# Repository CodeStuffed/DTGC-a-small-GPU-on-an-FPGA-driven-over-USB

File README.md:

# DTGC: a small GPU on an FPGA, driven over USB

DTGC is a graphics chip I am building on the Sipeed Tang Nano 20K FPGA board. A PC sends drawing commands over USB, the FPGA draws into memory, and the picture goes out over HDMI to a monitor.

**Status: nothing has run on real hardware yet.** Every result here comes from simulation (running the Verilog on a PC) or from the emulator (a Python copy of the GPU). "Passes simulation" never means "works on the board". Real results go in [docs/test-log.md](docs/test-log.md).

## The plan

1. **Basics.** Install free open-source FPGA tools, read the board's schematic, blink an LED, show colour bars over HDMI, and keep a picture in the board's SDRAM memory.
2. **Talk to a PC.** A USB protocol with checksums and retries, a parser on the FPGA, and a Python emulator of the GPU so software can be tested without a board.
3. **Draw in 3D.** A triangle rasterizer with depth test, colour blending and textures, then a spinning cube demo.
4. **Make it fast.** Measure a frame in simulation and remove the slowest parts one at a time.
5. **HD output.** 720p and 1080p, with an upscaler so 1080p fits the board's memory and speed. Target: 1080p at 30 fps.
6. **Make it useful.** An app window, small games, a graphics API, and a small Direct3D 9 bridge for old programs.
7. **Faster USB.** Windows and Linux app packages, and a link through an FT2232H USB 2.0 chip, much faster than the board's own serial port.
8. **A board for the fast link.** A small 4-layer "backpack" PCB with the FT2232H that plugs on top of the Tang Nano 20K.
9. **Ready to order.** A 3D-printed case, the files an assembly service needs, and a line-by-line check of the schematic against the chip's datasheet.
10. **Wrap up.** How to run and test everything, then real hardware tests.

Rules for the whole project: free tools only, every Verilog module gets a testbench, and no pin or voltage is guessed. Anything not yet confirmed is marked VERIFY.

## Progress log

Each update below was added when that step was finished. Older updates stay as they were written.

<!-- part 1 -->
### Update 1: Tools, first blink, colour bars and memory

The starting point: free tools, a check that they support this board, and the first three pieces of hardware design.

- **Tools.** Only free open-source tools: Yosys, nextpnr-himbaechel with Apicula, openFPGALoader and Icarus Verilog, all from the OSS CAD Suite. No vendor tools. Install steps are in [docs/setup.md](docs/setup.md), installed versions in [tools/versions.md](tools/versions.md), and what to buy in [docs/shopping-list.md](docs/shopping-list.md).
- **Board research.** Pins come from Sipeed's schematic, not from guesses. Any pin, voltage or timing not yet confirmed is marked VERIFY in [docs/verify.md](docs/verify.md). The pins used are in [docs/board/pins-needed.md](docs/board/pins-needed.md).
- **Blink an LED** (`rtl/blink.v`). The smallest test that the build and flash chain works. Passes simulation and the bitstream builds.
- **640x480 HDMI colour bars** (`rtl/video_timing.v`, `rtl/tmds_encoder.v`, `rtl/hdmi_out.v`). Screen timing plus TMDS, the encoding HDMI uses for each colour wire. Passes simulation and the bitstream builds.
- **SDRAM framebuffer** (`rtl/sdram_ctrl.v`, `rtl/fb_scanout.v`). The picture is kept in the board's SDRAM memory and read out to the screen. A memory model fails the test on any broken timing rule. Writing it found two mistakes: too few memory refreshes in the first plan, and stray pixels after reset.

The overall plan is in [docs/design-plan.md](docs/design-plan.md) and the milestone list in [docs/roadmap.md](docs/roadmap.md).

Next: get commands from a PC into the GPU, and a way to test without a board.

<!-- part 2 -->
### Update 2: USB protocol, emulator and tests

The GPU learns to take commands from a PC, and everything gets a test.

- **Protocol** ([docs/protocol.md](docs/protocol.md)). Binary packets with checksums, sequence numbers and retries. On the FPGA, `rtl/uart_rx.v` receives, `rtl/pkt_parser.v` checks each packet and `rtl/cmd_exec.v` runs it. The first UART version cut the stop bit short; the tests caught it.
- **Emulator** (`sw/dtgc/emulator.py`). A Python copy of the GPU that speaks the same protocol over TCP. It matches the Verilog bit for bit on random command streams, so software can be written and tested with no board.
- **Library and command line** (`sw/dtgc/`). Finds the board, or falls back on the emulator. Has a self-test, and record and replay.
- **Tests.** `python scripts/run_tests.py --quick` runs everything. [scripts/mutation_check.py](scripts/mutation_check.py) plants one bug at a time in the Verilog and checks that some test fails.
- **Saving link bandwidth.** Only changed tiles are sent, with run-length compression. A benchmark mode measures it: from 9 bytes per frame for a still picture up to 120,522 bytes for noise ([docs/benchmarks.md](docs/benchmarks.md)).

Next: draw triangles.

<!-- part 3 -->
### Update 3: Drawing triangles in 3D

- **Triangle rasterizer** (`rtl/raster.v`, [docs/rasterizer.md](docs/rasterizer.md)). Fixed-point maths for the triangle edges, colour blended across each triangle, a depth test so nearer things hide farther ones, and textures. Bit for bit the same as the Python reference.
- **Dither** ([docs/windows-and-color-options.md](docs/windows-and-color-options.md)). Smoother colour from few bits: 42.1 dB against 21.8 dB without dither.
- **Spinning cube demo.** `python -m sw.dtgc spin`. The picture above is what the Verilog drew in simulation, and it matches the emulator.

Size and speed of every build is recorded in [docs/resources.md](docs/resources.md).

Next: make drawing faster.

<!-- part 4 -->
### Update 4: Making it faster

Five speed steps, each measured in simulation on the same cube frame (340x340 picture):

| Step | Cube frame |
|---|---|
| Starting point (25.2 MHz clock) | about 46 ms |
| Keep SDRAM rows open | about 16 ms |
| One pixel per clock, burst depth reads | about 8 ms |
| Faster clears | about 5 ms |
| Fast depth clear, posted writes, skip empty space | 205,978 clocks down to about 88,000 |

Last, the drawing clock went from about 26 MHz to 46.41 and 48 MHz. That passes the timing estimate and simulation. The SDRAM pin timing is not checked yet (VERIFY).

Next: higher resolutions, up to 1080p.

<!-- part 5 -->
### Update 5: HD output and 1080p30

- **More resolutions.** 1280x720 at 60 Hz and 1920x1080 at 50 Hz. The fast serial clocks these need are untested against the chip's limits (VERIFY).
- **Upscalers** ([docs/upscale.md](docs/upscale.md)). A Python model first (DT-Upscale), then a bilinear upscaler and an edge-directed x2 upscaler in Verilog. Both match the model bit for bit. No neural networks.
- **Indexed triangle lists.** A corner shared by several triangles is sent once. The 1148-triangle field scene needs 3.43 times fewer bytes.
- **1080p at 30 fps** ([docs/architecture-1080p30.md](docs/architecture-1080p30.md)). The GPU draws a 960x540 picture and the edge upscaler doubles it to 1920x1080 on the way out. Drawing every pixel at full size does not fit the board's memory or time ([docs/hd-limits.md](docs/hd-limits.md)).

```mermaid
flowchart LR
  PC["PC app"] -- "USB" --> RX["Link and packet parser"]
  RX --> EXEC["Command executor"]
  EXEC --> RAST["Triangle rasterizer"]
  EXEC --> SDRAM[("SDRAM<br/>colour + depth")]
  RAST --> SDRAM
  SDRAM --> SCAN["Scan-out"]
  SCAN --> UP["Upscaler x2"]
  UP --> TMDS["HDMI encoder"]
  TMDS --> MON["Monitor"]
  EXEC -- replies --> PC
```

Two clock domains: drawing at 46.41 MHz, video at 74.25 MHz with a 371.25 MHz serial clock.

| Measured in simulation | Result |
|---|---|
| Spinning cube, 1080p30 build | 255,780 clocks, 5.51 ms |
| Field of 1148 triangles, 1080p30 build | 1,521,436 clocks, 32.8 ms, 30.5 fps (1.6% inside the budget) |
| Largest build, `top_gpu_1080p30` | 12,740 of 20,736 LUTs (61%), 10 of 46 block RAMs, core clock estimate 54.52 MHz (needs 46.41) |

What to check first on a real board: [docs/first-hardware.md](docs/first-hardware.md).

Next: an app and a graphics API so programs can use the GPU.

<!-- part 6 -->
### Update 6: Apps, games and the graphics API

- **Shader** (`rtl/shade_pipe.v`). A pipelined fixed-point shader that matches its model bit for bit. Built and tested, not yet connected to the GPU.
- **App and games.** `python -m sw.dtgc app` opens one window for everything. `python -m sw.dtgc play pong` runs a game. Tested on the emulator only.
- **Graphics API** ([docs/api.md](docs/api.md)). Canvas, meshes and frames for your own programs.
- **Three versions** ([docs/versions.md](docs/versions.md)). One app runs all three:

| | This PC only | Board, HDMI out | Board, USB out |
|---|---|---|---|
| What you need | Nothing extra | Tang Nano 20K, HDMI cable, monitor | Tang Nano 20K |
| Who draws | The PC's own graphics card | The FPGA | The FPGA |
| Where the picture goes | A window | A monitor | A window on the PC |

- **Direct3D 9 subset** ([docs/direct3d.md](docs/direct3d.md)). A small `d3d9.dll` so some old fixed-function Direct3D 9 programs can draw on DTGC. Modern games will not run.

Next: app packages and a faster USB link.

<!-- part 7 -->
### Update 7: Windows packages and the fast USB link

- **Windows device** ([docs/windows-device.md](docs/windows-device.md)). A software device so DTGC shows in Device Manager. Untested, because it needs admin rights.
- **App packages** ([docs/driver-app.md](docs/driver-app.md)). `scripts/package_windows.py` builds a portable `dtgc.exe` (its self-test passes). `scripts/package_linux.py` builds a Linux package, which has not been run on Linux.
- **FT2232H link** (`rtl/ft_link.v`, `rtl/top_gpu_ft.v`). The board's own USB serial port is assumed at about 0.3 MB/s (not yet measured), which gives about 19.5 fps for the field scene. The FT2232H chip moves 8 bits at a time at 60 MHz, up to about 40 MB/s by its datasheet. The whole GPU with this link passes simulation. It must pass the breakout test in [docs/ft2232h-test.md](docs/ft2232h-test.md) before any board is ordered.

Next: a small board that carries the fast USB chip.

<!-- part 8 -->
### Update 8: The xDTGC backpack board

A small 4-layer board that plugs on top of the Tang Nano 20K and carries the FT2232H. One USB-C cable powers both boards and carries the data. It does not add drawing power or change the HDMI resolution; it only makes the link faster.

| Item | Value |
|---|---|
| Size | 54.04 x 25 mm, the same length as the Tang Nano 20K |
| Layers | 4: top signals, ground, 3.3 V, bottom signals |
| Main chips | FT2232HL (USB to FIFO), 93LC56B (settings memory), AP2114H-3.3 (3.3 V regulator) |
| Protection | 500 mA resettable fuse, USB ESD diode, Schottky diode so two USB cables cannot fight |
| Fitting | Two 1x20 sockets underneath plug onto the Tang's pins |
| Files | `pcb/backpack/tinygpu_backpack.kicad_sch` (schematic) and `pcb/backpack/tinygpu_backpack.kicad_pcb` (layout), KiCad 10 |

The layout is made by scripts, so it can be rebuilt the same way every time: `scripts/pcb_place.py` places the parts and `scripts/pcb_route.py` routes them. The schematic rule check gives 0 errors and the layout rule check 0 errors, 0 unconnected. The layout review list is [docs/pcb-layout-review.md](docs/pcb-layout-review.md), and how assembly services work is in [docs/pcb-assembly.md](docs/pcb-assembly.md).

Next: a case, the order files, and a careful check of the schematic.

<!-- part 9 -->
### Update 9: Case, order files and datasheet review

- **Case** (`pcb/case/`, [docs/case.md](docs/case.md)). A 3D-printable tray and lid. Its sizes are placeholders until the real boards are measured, so do not print it yet.
- **Order files** (`pcb/backpack/quote/`). Gerbers, BOM and part positions, made by `python scripts/pcb_quote_pack.py`, which stops if the rule check finds any error. 39 parts on 20 BOM lines, about USD 12.86 per board at cached prices. Not a quote, and stock is not checked. Quote notes: [docs/pcbway-quote.md](docs/pcbway-quote.md).
- **Datasheet review.** The schematic was checked line by line against the FT2232H datasheet (version 2.3). That fixed four mistakes the automatic checks passed: two filter capacitors on the wrong side of their beads, the settings-memory pull-up on the wrong side of its resistor, the reset pin tied straight to 3.3 V, and a regulator that needed capacitors this board does not use. The board was then re-routed with no vias inside pads: 122 vias, 0.20 mm drill. The USB pair is 0.25 mm tracks with a 0.25 mm gap, about 93 ohm by hand formula (target 90). Lessons from all this: [docs/lessons.md](docs/lessons.md).

Before ordering:

1. Test the FT2232H on a breakout module with jumper wires ([docs/ft2232h-test.md](docs/ft2232h-test.md)). Expected: data passes both ways with no errors. If it fails, do not order.
2. Measure the real Tang Nano 20K. Expected: 20.32 mm between the two pin rows, and the tallest part lower than the 8.5 mm sockets.
3. Review the layout with [docs/pcb-layout-review.md](docs/pcb-layout-review.md).
4. Get a quote. Expected: the fab accepts the 0.20 mm vias and gives a USB pair impedance near 90 ohm.
5. Check stock of all 20 BOM lines on order day.

After the boards arrive, test them with [docs/pcb-home-test.md](docs/pcb-home-test.md).

Next: write up how to run everything.

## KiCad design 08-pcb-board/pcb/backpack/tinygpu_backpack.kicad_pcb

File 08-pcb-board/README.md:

# DTGC: a small GPU on an FPGA, driven over USB

DTGC is a graphics chip I am building on the Sipeed Tang Nano 20K FPGA board. A PC sends drawing commands over USB, the FPGA draws into memory, and the picture goes out over HDMI to a monitor.

**Status: nothing has run on real hardware yet.** Every result here comes from simulation (running the Verilog on a PC) or from the emulator (a Python copy of the GPU). "Passes simulation" never means "works on the board". Real results go in [docs/test-log.md](docs/test-log.md).

## The plan

1. **Basics.** Install free open-source FPGA tools, read the board's schematic, blink an LED, show colour bars over HDMI, and keep a picture in the board's SDRAM memory.
2. **Talk to a PC.** A USB protocol with checksums and retries, a parser on the FPGA, and a Python emulator of the GPU so software can be tested without a board.
3. **Draw in 3D.** A triangle rasterizer with depth test, colour blending and textures, then a spinning cube demo.
4. **Make it fast.** Measure a frame in simulation and remove the slowest parts one at a time.
5. **HD output.** 720p and 1080p, with an upscaler so 1080p fits the board's memory and speed. Target: 1080p at 30 fps.
6. **Make it useful.** An app window, small games, a graphics API, and a small Direct3D 9 bridge for old programs.
7. **Faster USB.** Windows and Linux app packages, and a link through an FT2232H USB 2.0 chip, much faster than the board's own serial port.
8. **A board for the fast link.** A small 4-layer "backpack" PCB with the FT2232H that plugs on top of the Tang Nano 20K.
9. **Ready to order.** A 3D-printed case, the files an assembly service needs, and a line-by-line check of the schematic against the chip's datasheet.
10. **Wrap up.** How to run and test everything, then real hardware tests.

Rules for the whole project: free tools only, every Verilog module gets a testbench, and no pin or voltage is guessed. Anything not yet confirmed is marked VERIFY.

## Progress log

Each update below was added when that step was finished. Older updates stay as they were written.

<!-- part 1 -->
### Update 1: Tools, first blink, colour bars and memory

The starting point: free tools, a check that they support this board, and the first three pieces of hardware design.

- **Tools.** Only free open-source tools: Yosys, nextpnr-himbaechel with Apicula, openFPGALoader and Icarus Verilog, all from the OSS CAD Suite. No vendor tools. Install steps are in [docs/setup.md](docs/setup.md), installed versions in [tools/versions.md](tools/versions.md), and what to buy in [docs/shopping-list.md](docs/shopping-list.md).
- **Board research.** Pins come from Sipeed's schematic, not from guesses. Any pin, voltage or timing not yet confirmed is marked VERIFY in [docs/verify.md](docs/verify.md). The pins used are in [docs/board/pins-needed.md](docs/board/pins-needed.md).
- **Blink an LED** (`rtl/blink.v`). The smallest test that the build and flash chain works. Passes simulation and the bitstream builds.
- **640x480 HDMI colour bars** (`rtl/video_timing.v`, `rtl/tmds_encoder.v`, `rtl/hdmi_out.v`). Screen timing plus TMDS, the encoding HDMI uses for each colour wire. Passes simulation and the bitstream builds.
- **SDRAM framebuffer** (`rtl/sdram_ctrl.v`, `rtl/fb_scanout.v`). The picture is kept in the board's SDRAM memory and read out to the screen. A memory model fails the test on any broken timing rule. Writing it found two mistakes: too few memory refreshes in the first plan, and stray pixels after reset.

The overall plan is in [docs/design-plan.md](docs/design-plan.md) and the milestone list in [docs/roadmap.md](docs/roadmap.md).

Next: get commands from a PC into the GPU, and a way to test without a board.

<!-- part 2 -->
### Update 2: USB protocol, emulator and tests

The GPU learns to take commands from a PC, and everything gets a test.

- **Protocol** ([docs/protocol.md](docs/protocol.md)). Binary packets with checksums, sequence numbers and retries. On the FPGA, `rtl/uart_rx.v` receives, `rtl/pkt_parser.v` checks each packet and `rtl/cmd_exec.v` runs it. The first UART version cut the stop bit short; the tests caught it.
- **Emulator** (`sw/dtgc/emulator.py`). A Python copy of the GPU that speaks the same protocol over TCP. It matches the Verilog bit for bit on random command streams, so software can be written and tested with no board.
- **Library and command line** (`sw/dtgc/`). Finds the board, or falls back on the emulator. Has a self-test, and record and replay.
- **Tests.** `python scripts/run_tests.py --quick` runs everything. [scripts/mutation_check.py](scripts/mutation_check.py) plants one bug at a time in the Verilog and checks that some test fails.
- **Saving link bandwidth.** Only changed tiles are sent, with run-length compression. A benchmark mode measures it: from 9 bytes per frame for a still picture up to 120,522 bytes for noise ([docs/benchmarks.md](docs/benchmarks.md)).

Next: draw triangles.

<!-- part 3 -->
### Update 3: Drawing triangles in 3D

- **Triangle rasterizer** (`rtl/raster.v`, [docs/rasterizer.md](docs/rasterizer.md)). Fixed-point maths for the triangle edges, colour blended across each triangle, a depth test so nearer things hide farther ones, and textures. Bit for bit the same as the Python reference.
- **Dither** ([docs/windows-and-color-options.md](docs/windows-and-color-options.md)). Smoother colour from few bits: 42.1 dB against 21.8 dB without dither.
- **Spinning cube demo.** `python -m sw.dtgc spin`. The picture above is what the Verilog drew in simulation, and it matches the emulator.

Size and speed of every build is recorded in [docs/resources.md](docs/resources.md).

Next: make drawing faster.

<!-- part 4 -->
### Update 4: Making it faster

Five speed steps, each measured in simulation on the same cube frame (340x340 picture):

| Step | Cube frame |
|---|---|
| Starting point (25.2 MHz clock) | about 46 ms |
| Keep SDRAM rows open | about 16 ms |
| One pixel per clock, burst depth reads | about 8 ms |
| Faster clears | about 5 ms |
| Fast depth clear, posted writes, skip empty space | 205,978 clocks down to about 88,000 |

Last, the drawing clock went from about 26 MHz to 46.41 and 48 MHz. That passes the timing estimate and simulation. The SDRAM pin timing is not checked yet (VERIFY).

Next: higher resolutions, up to 1080p.

<!-- part 5 -->
### Update 5: HD output and 1080p30

- **More resolutions.** 1280x720 at 60 Hz and 1920x1080 at 50 Hz. The fast serial clocks these need are untested against the chip's limits (VERIFY).
- **Upscalers** ([docs/upscale.md](docs/upscale.md)). A Python model first (DT-Upscale), then a bilinear upscaler and an edge-directed x2 upscaler in Verilog. Both match the model bit for bit. No neural networks.
- **Indexed triangle lists.** A corner shared by several triangles is sent once. The 1148-triangle field scene needs 3.43 times fewer bytes.
- **1080p at 30 fps** ([docs/architecture-1080p30.md](docs/architecture-1080p30.md)). The GPU draws a 960x540 picture and the edge upscaler doubles it to 1920x1080 on the way out. Drawing every pixel at full size does not fit the board's memory or time ([docs/hd-limits.md](docs/hd-limits.md)).

```mermaid
flowchart LR
  PC["PC app"] -- "USB" --> RX["Link and packet parser"]
  RX --> EXEC["Command executor"]
  EXEC --> RAST["Triangle rasterizer"]
  EXEC --> SDRAM[("SDRAM<br/>colour + depth")]
  RAST --> SDRAM
  SDRAM --> SCAN["Scan-out"]
  SCAN --> UP["Upscaler x2"]
  UP --> TMDS["HDMI encoder"]
  TMDS --> MON["Monitor"]
  EXEC -- replies --> PC
```

Two clock domains: drawing at 46.41 MHz, video at 74.25 MHz with a 371.25 MHz serial clock.

| Measured in simulation | Result |
|---|---|
| Spinning cube, 1080p30 build | 255,780 clocks, 5.51 ms |
| Field of 1148 triangles, 1080p30 build | 1,521,436 clocks, 32.8 ms, 30.5 fps (1.6% inside the budget) |
| Largest build, `top_gpu_1080p30` | 12,740 of 20,736 LUTs (61%), 10 of 46 block RAMs, core clock estimate 54.52 MHz (needs 46.41) |

What to check first on a real board: [docs/first-hardware.md](docs/first-hardware.md).

Next: an app and a graphics API so programs can use the GPU.

<!-- part 6 -->
### Update 6: Apps, games and the graphics API

- **Shader** (`rtl/shade_pipe.v`). A pipelined fixed-point shader that matches its model bit for bit. Built and tested, not yet connected to the GPU.
- **App and games.** `python -m sw.dtgc app` opens one window for everything. `python -m sw.dtgc play pong` runs a game. Tested on the emulator only.
- **Graphics API** ([docs/api.md](docs/api.md)). Canvas, meshes and frames for your own programs.
- **Three versions** ([docs/versions.md](docs/versions.md)). One app runs all three:

| | This PC only | Board, HDMI out | Board, USB out |
|---|---|---|---|
| What you need | Nothing extra | Tang Nano 20K, HDMI cable, monitor | Tang Nano 20K |
| Who draws | The PC's own graphics card | The FPGA | The FPGA |
| Where the picture goes | A window | A monitor | A window on the PC |

- **Direct3D 9 subset** ([docs/direct3d.md](docs/direct3d.md)). A small `d3d9.dll` so some old fixed-function Direct3D 9 programs can draw on DTGC. Modern games will not run.

Next: app packages and a faster USB link.

<!-- part 7 -->
### Update 7: Windows packages and the fast USB link

- **Windows device** ([docs/windows-device.md](docs/windows-device.md)). A software device so DTGC shows in Device Manager. Untested, because it needs admin rights.
- **App packages** ([docs/driver-app.md](docs/driver-app.md)). `scripts/package_windows.py` builds a portable `dtgc.exe` (its self-test passes). `scripts/package_linux.py` builds a Linux package, which has not been run on Linux.
- **FT2232H link** (`rtl/ft_link.v`, `rtl/top_gpu_ft.v`). The board's own USB serial port is assumed at about 0.3 MB/s (not yet measured), which gives about 19.5 fps for the field scene. The FT2232H chip moves 8 bits at a time at 60 MHz, up to about 40 MB/s by its datasheet. The whole GPU with this link passes simulation. It must pass the breakout test in [docs/ft2232h-test.md](docs/ft2232h-test.md) before any board is ordered.

Next: a small board that carries the fast USB chip.

<!-- part 8 -->
### Update 8: The xDTGC backpack board

A small 4-layer board that plugs on top of the Tang Nano 20K and carries the FT2232H. One USB-C cable powers both boards and carries the data. It does not add drawing power or change the HDMI resolution; it only makes the link faster.

| Item | Value |
|---|---|
| Size | 54.04 x 25 mm, the same length as the Tang Nano 20K |
| Layers | 4: top signals, ground, 3.3 V, bottom signals |
| Main chips | FT2232HL (USB to FIFO), 93LC56B (settings memory), AP2114H-3.3 (3.3 V regulator) |
| Protection | 500 mA resettable fuse, USB ESD diode, Schottky diode so two USB cables cannot fight |
| Fitting | Two 1x20 sockets underneath plug onto the Tang's pins |
| Files | `pcb/backpack/tinygpu_backpack.kicad_sch` (schematic) and `pcb/backpack/tinygpu_backpack.kicad_pcb` (layout), KiCad 10 |

The layout is made by scripts, so it can be rebuilt the same way every time: `scripts/pcb_place.py` places the parts and `scripts/pcb_route.py` routes them. The schematic rule check gives 0 errors and the layout rule check 0 errors, 0 unconnected. The layout review list is [docs/pcb-layout-review.md](docs/pcb-layout-review.md), and how assembly services work is in [docs/pcb-assembly.md](docs/pcb-assembly.md).

Next: a case, the order files, and a careful check of the schematic.

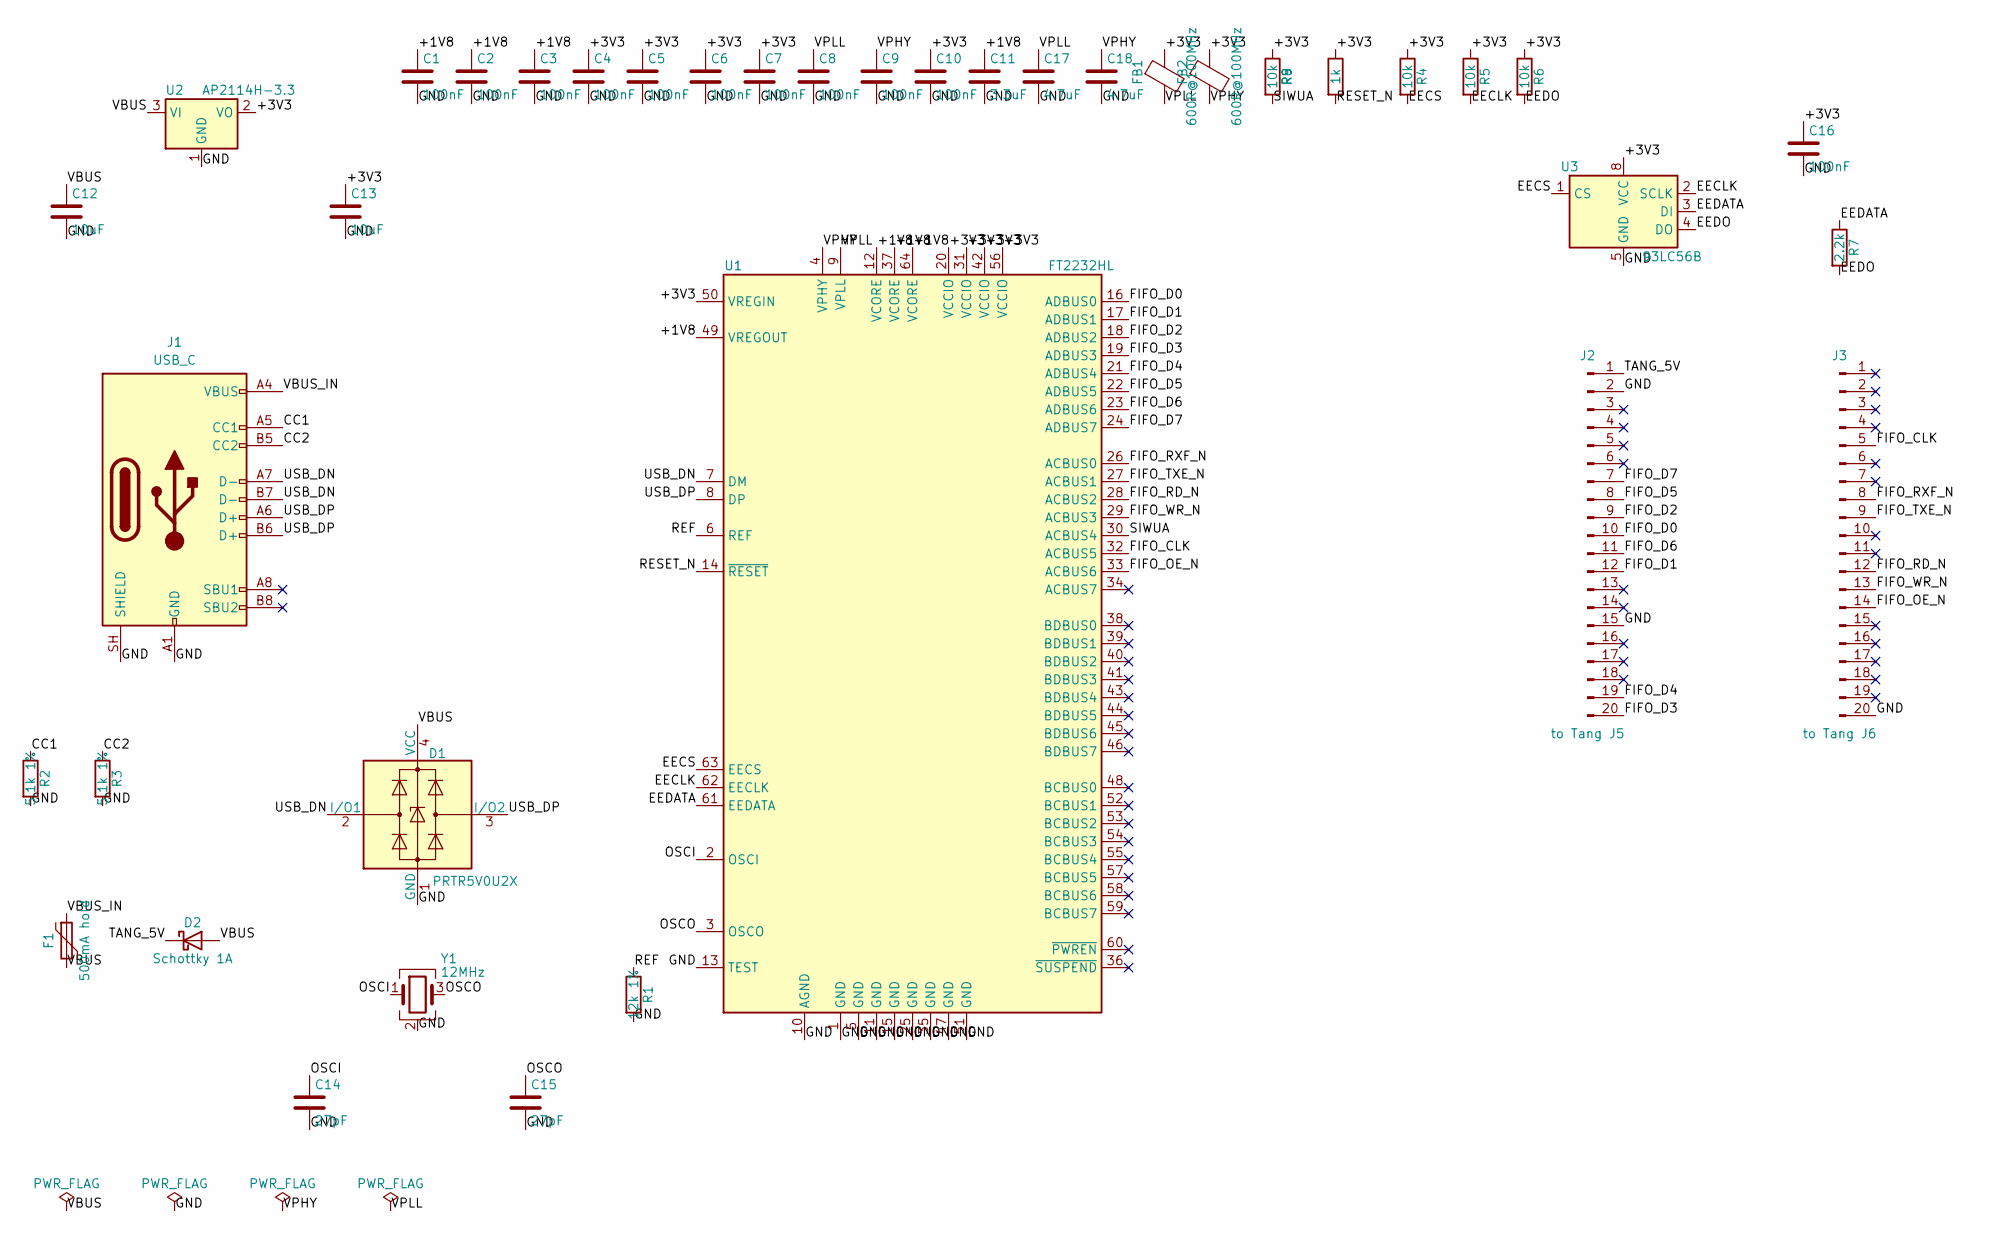
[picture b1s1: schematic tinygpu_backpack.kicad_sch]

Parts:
C1, C2, C3, C4, C5, C6, C7, C8, C9, C10, C16: 100nF; C_0402_1005Metric
C11: 3.3uF; C_0603_1608Metric
C12, C13: 10uF; C_0805_2012Metric
C14, C15: 27pF; C_0402_1005Metric
C17, C18: 4.7uF; C_0603_1608Metric
D1: PRTR5V0U2X; SOT-143
D2: Schottky 1A; D_SOD-123
F1: 500mA hold; Fuse_1206_3216Metric
FB1, FB2: 600R@100MHz; L_0603_1608Metric
J1: USB_C; USB_C_Receptacle_HRO_TYPE-C-31-M-12
J2: to Tang J5; PinSocket_1x20_P2.54mm_Vertical
J3: to Tang J6; PinSocket_1x20_P2.54mm_Vertical
R1: 12k 1%; R_0402_1005Metric
R2, R3: 5.1k 1%; R_0402_1005Metric
R4, R5, R6, R8: 10k; R_0402_1005Metric
R7: 2.2k; R_0402_1005Metric
R9: 1k; R_0402_1005Metric
U1: FT2232HL; LQFP-64_10x10mm_P0.5mm
U2: AP2114H-3.3; SOT-223-3_TabPin2
U3: 93LC56B; SOIC-8_3.9x4.9mm_P1.27mm
Y1: 12MHz; Crystal_SMD_3225-4Pin_3.2x2.5mm

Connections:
/+1V8: C1.1, C2.1, C3.1, C11.1, U1.12 (VCORE), U1.37 (VCORE), U1.49 (VREGOUT), U1.64 (VCORE)
/+3V3: C4.1, C5.1, C6.1, C7.1, C10.1, C13.1, C16.1, FB1.1, FB2.1, R4.1, R5.1, R6.1, R8.1, R9.1, U1.20 (VCCIO), U1.31 (VCCIO), U1.42 (VCCIO), U1.50 (VREGIN), U1.56 (VCCIO), U2.2 (VO), U3.8 (VCC)
/CC1: J1.A5 (CC1), R2.1
/CC2: J1.B5 (CC2), R3.1
/EECLK: R5.2, U1.62 (EECLK), U3.2 (SCLK)
/EECS: R4.2, U1.63 (EECS), U3.1 (CS)
/EEDATA: R7.1, U1.61 (EEDATA), U3.3 (DI)
/EEDO: R6.2, R7.2, U3.4 (DO)
/FIFO_CLK: J3.5, U1.32 (ACBUS5)
/FIFO_D0: J2.10, U1.16 (ADBUS0)
/FIFO_D1: J2.12, U1.17 (ADBUS1)
/FIFO_D2: J2.9, U1.18 (ADBUS2)
/FIFO_D3: J2.20, U1.19 (ADBUS3)
/FIFO_D4: J2.19, U1.21 (ADBUS4)
/FIFO_D5: J2.8, U1.22 (ADBUS5)
/FIFO_D6: J2.11, U1.23 (ADBUS6)
/FIFO_D7: J2.7, U1.24 (ADBUS7)
/FIFO_OE_N: J3.14, U1.33 (ACBUS6)
/FIFO_RD_N: J3.12, U1.28 (ACBUS2)
/FIFO_RXF_N: J3.8, U1.26 (ACBUS0)
/FIFO_TXE_N: J3.9, U1.27 (ACBUS1)
/FIFO_WR_N: J3.13, U1.29 (ACBUS3)
/GND: C1.2, C2.2, C3.2, C4.2, C5.2, C6.2, C7.2, C8.2, C9.2, C10.2, C11.2, C12.2, C13.2, C14.2, C15.2, C16.2, C17.2, C18.2, D1.1 (GND), J1.A1 (GND), J1.A12 (GND), J1.B1 (GND), J1.B12 (GND), J1.SH (SHIELD), J2.2, J2.15, J3.20, R1.2, R2.2, R3.2, U1.1 (GND), U1.5 (GND), U1.10 (AGND), U1.11 (GND), U1.13 (TEST), U1.15 (GND), U1.25 (GND), U1.35 (GND), U1.47 (GND), U1.51 (GND), U2.1 (GND), U3.5 (GND), Y1.2 (G), Y1.4 (G)
/OSCI: C14.1, U1.2 (OSCI), Y1.1
/OSCO: C15.1, U1.3 (OSCO), Y1.3
/REF: R1.1, U1.6 (REF)
/RESET_N: R9.2, U1.14 (~RESET)
/SIWUA: R8.2, U1.30 (ACBUS4)
/TANG_5V: D2.1 (K), J2.1
/USB_DN: D1.2 (I/O1), J1.A7 (D-), J1.B7 (D-), U1.7 (DM)
/USB_DP: D1.3 (I/O2), J1.A6 (D+), J1.B6 (D+), U1.8 (DP)
/VBUS: C12.1, D1.4 (VCC), D2.2 (A), F1.2, U2.3 (VI)
/VBUS_IN: F1.1, J1.A4 (VBUS), J1.A9 (VBUS), J1.B4 (VBUS), J1.B9 (VBUS)
/VPHY: C9.1, C18.1, FB2.2, U1.4 (VPHY)
/VPLL: C8.1, C17.1, FB1.2, U1.9 (VPLL)

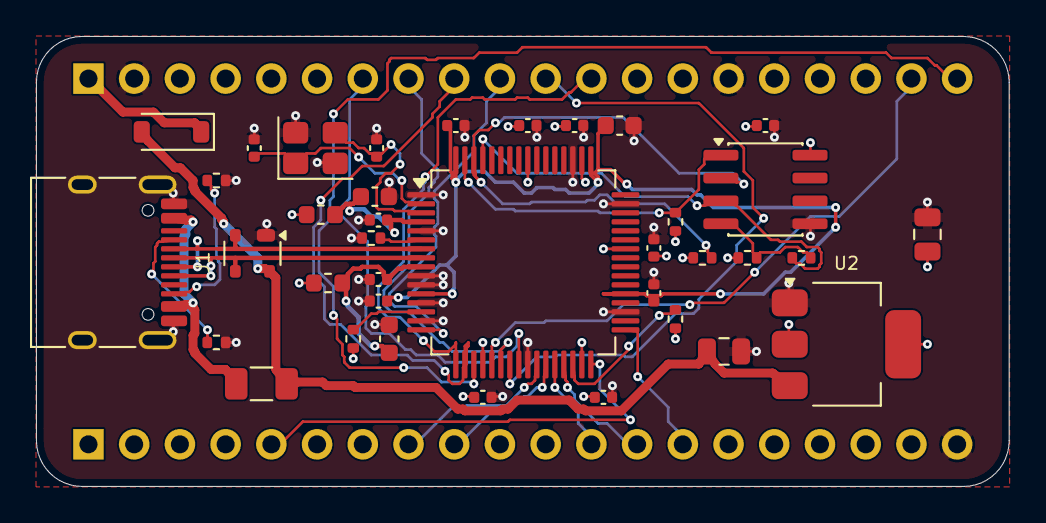
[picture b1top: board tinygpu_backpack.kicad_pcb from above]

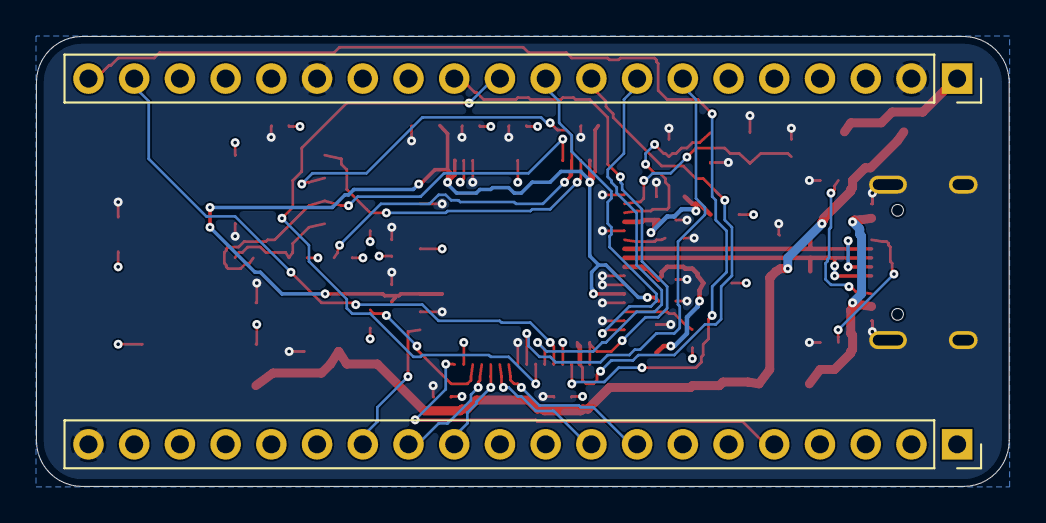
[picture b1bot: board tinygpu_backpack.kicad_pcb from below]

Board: 4 copper layers, 54.0 x 25.0 mm, 39 parts (2 on the bottom side), 35 nets.
